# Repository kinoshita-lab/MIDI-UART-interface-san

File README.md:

# MIDI-UART interface-san Kit

MIDI UART interface-san is a handy interface PCB for MIDI and microcontrollers with commonly used basic circuit when you start developping  MIDI-related  MCU project, e.g. TRS jacks for MIDI I/O, optocouplers, digital buffers, etc. It means by using this PCB, you do not have to repeat soldering/making a breadboard for these purpose anymore.

You can choose both 5V and 3.3V for power supply(can be selected jumper pins), to match the voltage of the MCU you want to use.

## Kit contents

- Pre-assembled circuit board
- 3.5mm TRS Jack connectors (J1, J2)
- 1x3P Pin Headers(J3, J4)
- 1x4P Pin Socket(CN1)
- Jumper pins(yellow) 2pcs.
- MIDI DIN <-> TRS(3.5mm) conversion cable(A type) 2pcs.

## How to assemble

Solder all of the jacks and connectors on the circuit board.
Please refer to the following image.

## How to use

- Select operation voltage by shorting Jumper pins on J3, J4. By shorting above two pins for 5V, bottom two pins for 3.3V.
- Connect V+ and GND to the circuit board, breadboard, or something you want to use with this product.
- Connect `In->` to the MCU's MIDI Input.
- Connect `Out->` to the MCU's MIDI Output.

## Schematics, design data, etc

<https://github.com/kinoshita-lab/MIDI-UART-interface-san>

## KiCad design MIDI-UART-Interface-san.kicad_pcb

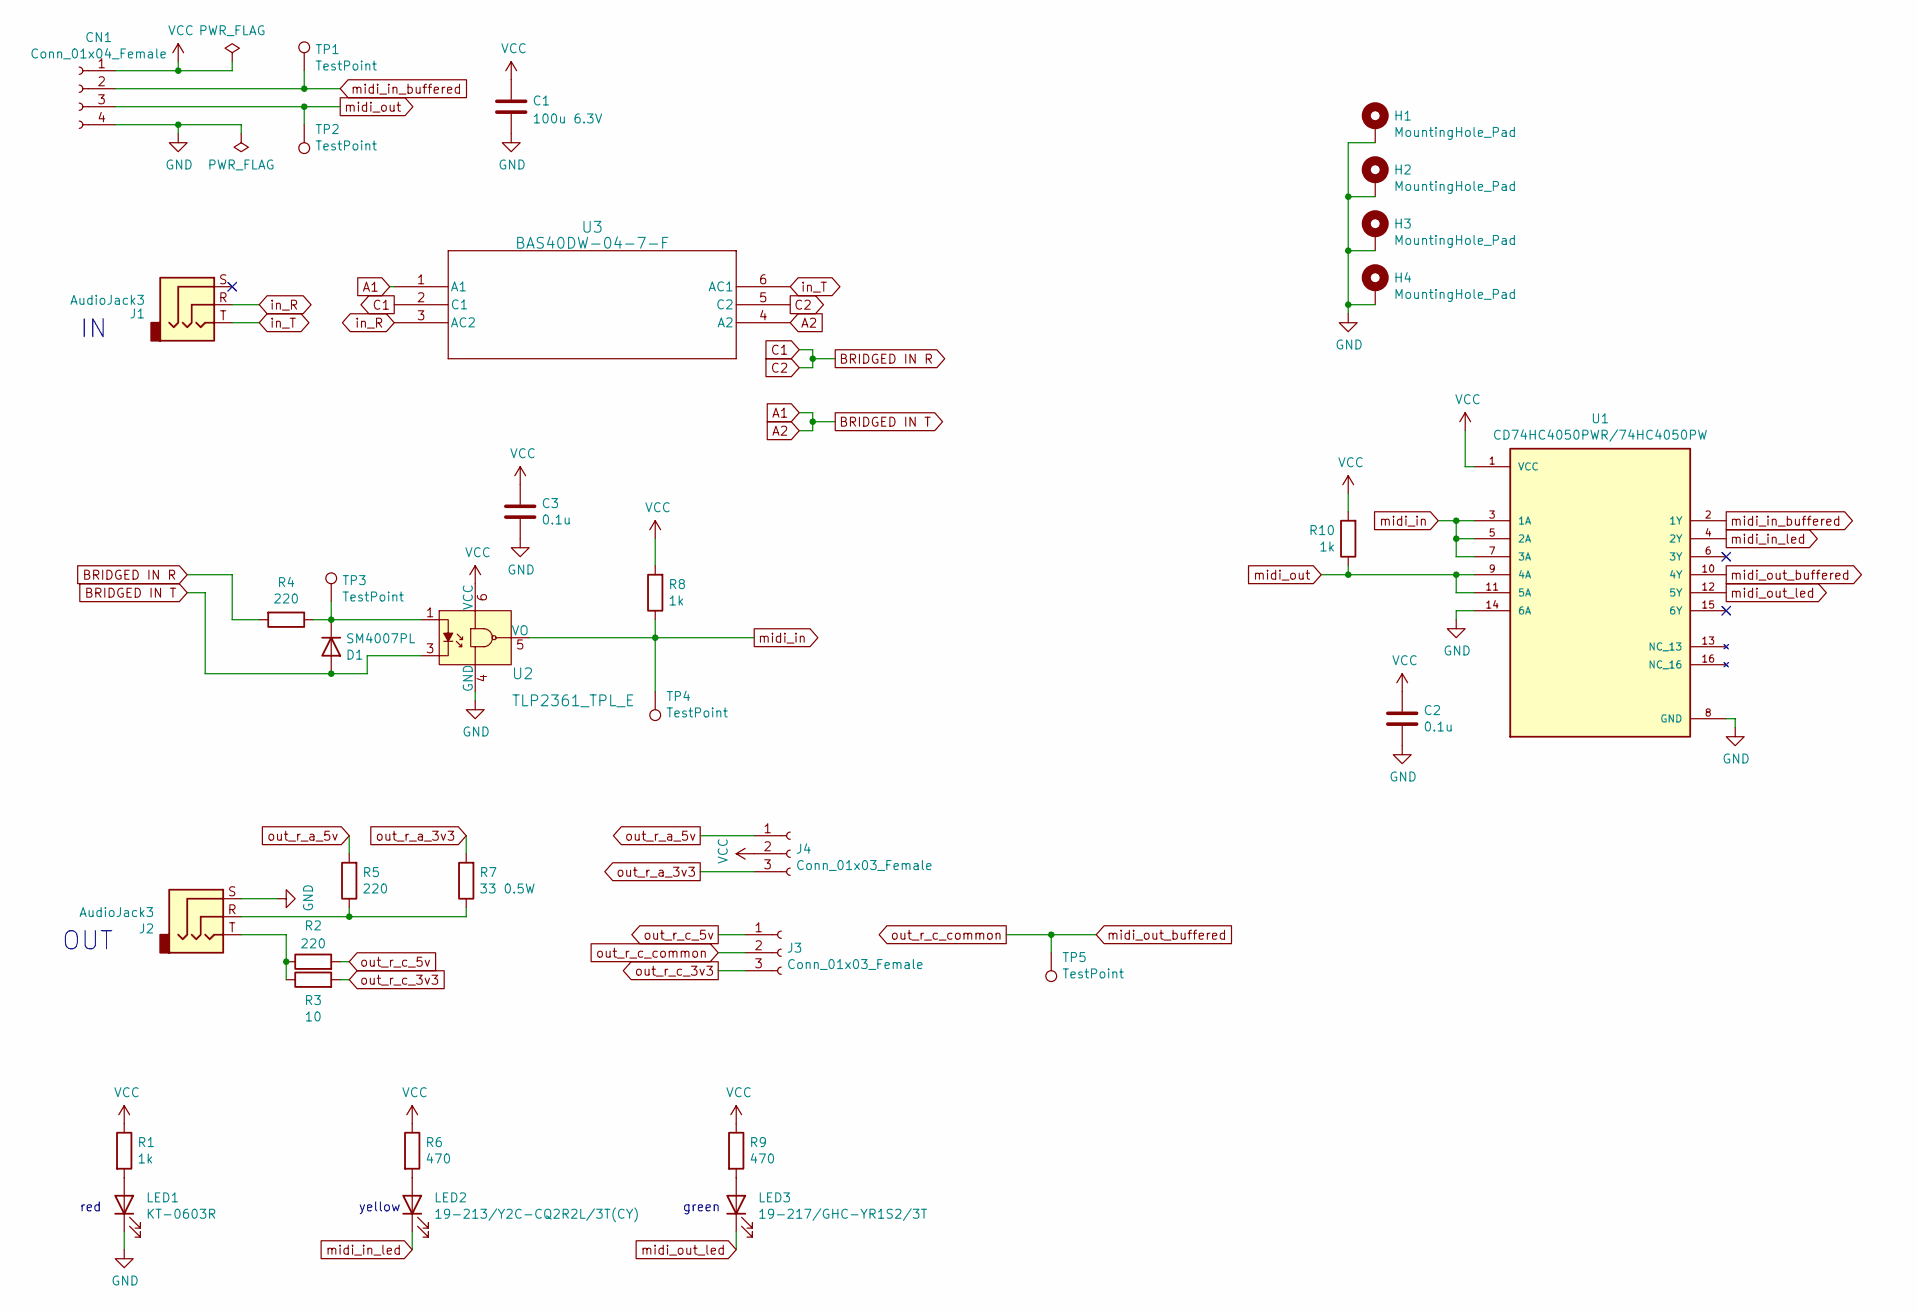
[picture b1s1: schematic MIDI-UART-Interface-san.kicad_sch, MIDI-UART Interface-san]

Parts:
C1: 100u 6.3V; C_1206_3216Metric_Pad1.33x1.80mm_HandSolder; LCSC C15008
C2, C3: 0.1u; C_0603_1608Metric_Pad1.08x0.95mm_HandSolder; LCSC C14663
CN1: Conn_01x04_Female; PinHeader_1x04_P2.54mm_Vertical; LCSC C124413
D1: SM4007PL; D_SOD-123; LCSC C64898
H1, H2, H3, H4: MountingHole_Pad; MountingHole_3.2mm_M3_ISO7380_Pad
J1, J2: AudioJack3; 3.5mm_Stereo_TRS_PJ-3210-4A_and_ST-005-G; LCSC C136686
J3, J4: Conn_01x03_Female; PinHeader_1x03_P2.54mm_Vertical; LCSC C49257
LED1: KT-0603R; LED_0603_1608Metric_Pad1.05x0.95mm_HandSolder; LCSC C965799
LED2: 19-213/Y2C-CQ2R2L/3T(CY); LED_0603_1608Metric_Pad1.05x0.95mm_HandSolder; LCSC C72038
LED3: 19-217/GHC-YR1S2/3T; LED_0603_1608Metric_Pad1.05x0.95mm_HandSolder; LCSC C72043
R1: 1k; R_0603_1608Metric_Pad1.05x0.95mm_HandSolder; LCSC C21190
R2, R4, R5: 220; R_1206_3216Metric_Pad1.30x1.75mm_HandSolder; LCSC C17957
R3: 10; R_1206_3216Metric_Pad1.30x1.75mm_HandSolder; LCSC C17903
R6, R9: 470; R_0603_1608Metric_Pad1.05x0.95mm_HandSolder; LCSC C21190
R7: 33 0.5W; R_1210_3225Metric_Pad1.30x2.65mm_HandSolder; LCSC C407192
R8: 1k; R_0603_1608Metric_Pad0.98x0.95mm_HandSolder; LCSC C22962
R10: 1k; R_0603_1608Metric_Pad1.05x0.95mm_HandSolder; LCSC C25804
TP1, TP2, TP3, TP4, TP5: TestPoint; TP_1PAD
U1: CD74HC4050PWR/74HC4050PW; SOP65P640X120-16N; PARTREV February 2005; LCSC C546991
U2: TLP2361_TPL_E; SO-5_4.4x3.6mm_P1.27mm; MPN TLP2361(TPL,E; Digi-Key_PN TLP2361(TPLECT-ND
U3: BAS40DW-04-7-F; SOT-363_DIO; LCSC C134364

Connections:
A1: D1.2 (A), U2.3, U3.1 (A1), U3.4 (A2)
BRIDGED IN R: R4.2, U3.2 (C1), U3.5 (C2)
GND: C1.2, C2.2, C3.2, CN1.4, H1.1, H2.1, H3.1, H4.1, J2.S, LED1.1 (K), U1.8 (GND), U1.14 (6A), U2.4 (GND)
unnamed: D1.1 (K), R4.1, TP3.1, U2.1
unnamed: J2.R, R5.1, R7.1
unnamed: J2.T, R2.1, R3.1
unnamed: LED1.2 (A), R1.2
unnamed: LED2.2 (A), R6.2
unnamed: LED3.2 (A), R9.2
VCC: C1.1, C2.1, C3.1, CN1.1, J4.2, R1.1, R6.1, R8.2, R9.1, R10.2, U1.1 (VCC), U2.6 (VCC)
in_R: J1.R, U3.3 (AC2)
in_T: J1.T, U3.6 (AC1)
midi_in: R8.1, TP4.1, U1.3 (1A), U1.5 (2A), U1.7 (3A), U2.5 (VO)
midi_in_buffered: CN1.2, TP1.1, U1.2 (1Y)
midi_in_led: LED2.1 (K), U1.4 (2Y)
midi_out: CN1.3, R10.1, TP2.1, U1.9 (4A), U1.11 (5A)
midi_out_buffered: J3.2, TP5.1, U1.10 (4Y)
midi_out_led: LED3.1 (K), U1.12 (5Y)
out_r_a_3v3: J4.3, R7.2
out_r_a_5v: J4.1, R5.2
out_r_c_3v3: J3.3, R3.2
out_r_c_5v: J3.1, R2.2

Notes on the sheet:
red
yellow
OUT
green

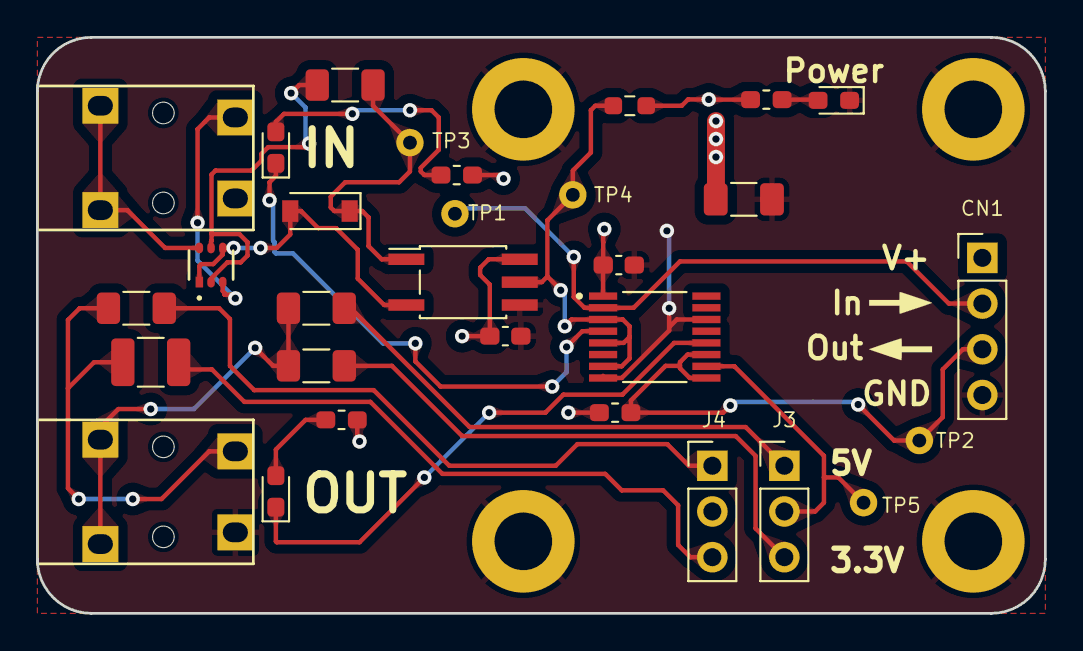
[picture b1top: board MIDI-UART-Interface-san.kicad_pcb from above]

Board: 2 copper layers, 56.0 x 32.0 mm, 34 parts (0 on the bottom side), 22 nets.

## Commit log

2021-06-09 add docs stub
2021-06-09 add kicad files from draft repository(w/ some renamings).
2021-06-09 replace pcb w/ renamed footprints.
2021-07-26 add image
2021-07-26 remove unused files
2021-12-09 Fix a typo
2022-04-14 add details for README
2024-06-22 Update to revision 2
2025-03-18 Revise to 2.1, KiCad 9.0
